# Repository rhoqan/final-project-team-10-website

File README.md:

**<h1 style="text-align:center;"> Improving Pedestrian Safety at Intersections</h1>**
    
<h3 style="text-align:center;"> Shlok Damani, Ryan Ho, Aarav Masrani, Dibyesh Sahoo</h3>

<h3 style="text-align:center;"> Fall 2024</h3>

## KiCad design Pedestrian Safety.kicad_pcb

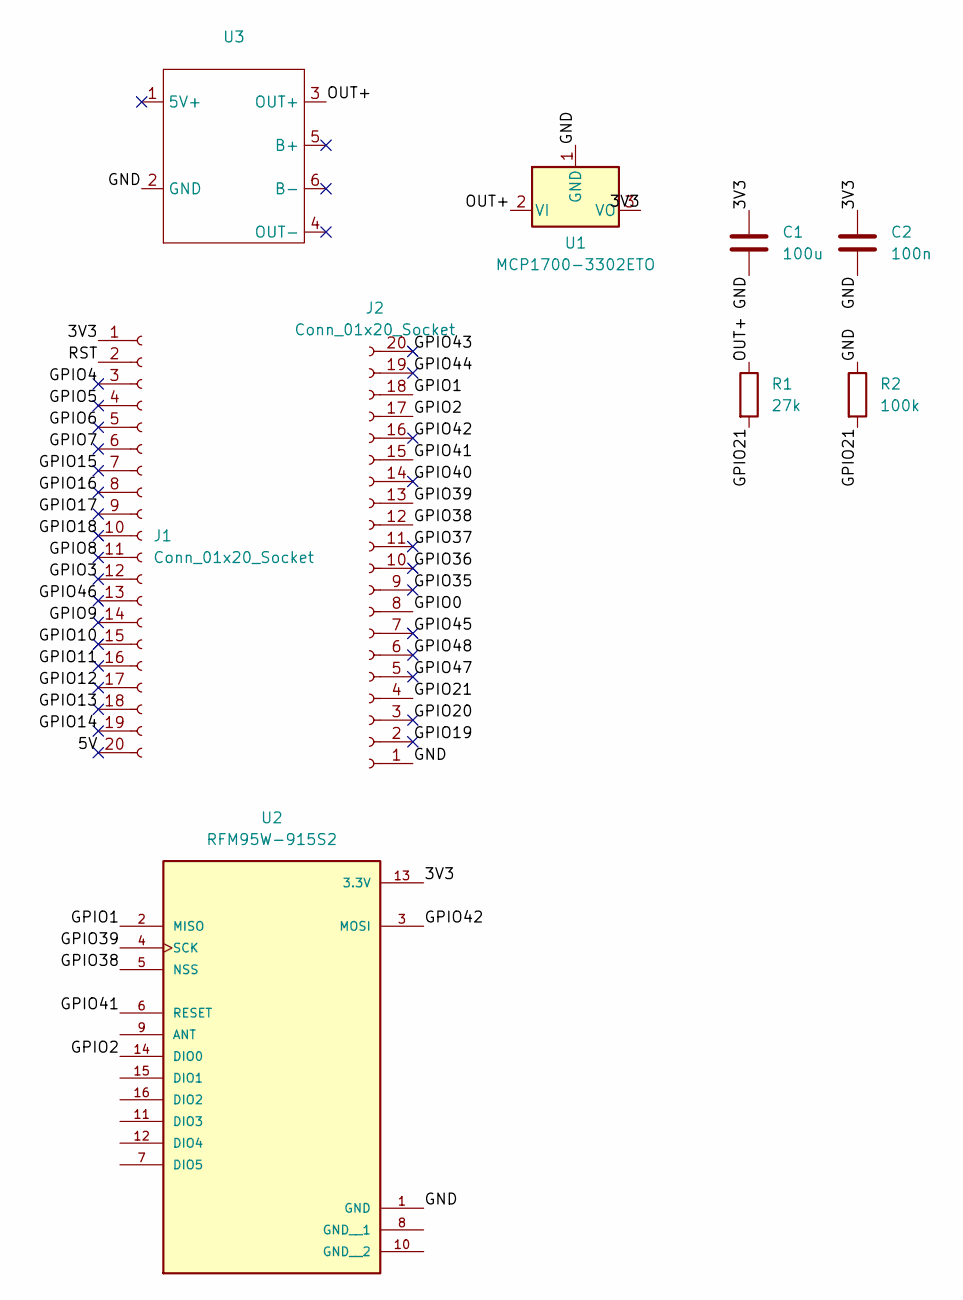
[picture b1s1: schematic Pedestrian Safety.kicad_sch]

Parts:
C1: 100u; CP_Elec_6.3x5.7; Digikey Part Number 732-8419-1-ND
C2: 100n; C_0603_1608Metric; Digikey PN: 1276-1013-1-ND
J1, J2: Conn_01x20_Socket; PinHeader_1x20_P2.54mm_Vertical
R1: 27k; R_0603_1608Metric; Digikey PN: P27.0KHCT-ND
R2: 100k; R_0603_1608Metric; Digikey PN: 311-100KGRCT-ND
U1: MCP1700-3302ETO; TO-92_MC_MCH; Digikey PN: MCP1700-3302E/TO-ND
U2: RFM95W-915S2; XCVR_RFM95W-915S2
U3: TP4056-18650

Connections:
/3V3: C1.1, C2.1, J1.1, U1.3 (VO), U2.13 (3.3V)
/5V: J1.20
/GND: C1.2, C2.2, J2.1, R2.1, U1.1 (GND), U2.1 (GND), U3.2 (GND)
/GPIO0: J2.8
/GPIO1: J2.18, U2.2 (MISO)
/GPIO2: J2.17, U2.14 (DIO0)
/GPIO3: J1.12
/GPIO4: J1.3
/GPIO5: J1.4
/GPIO6: J1.5
/GPIO7: J1.6
/GPIO8: J1.11
/GPIO9: J1.14
/GPIO10: J1.15
/GPIO11: J1.16
/GPIO12: J1.17
/GPIO13: J1.18
/GPIO14: J1.19
/GPIO15: J1.7
/GPIO16: J1.8
/GPIO17: J1.9
/GPIO18: J1.10
/GPIO19: J2.2
/GPIO20: J2.3
/GPIO21: J2.4, R1.2, R2.2
/GPIO35: J2.9
/GPIO36: J2.10
/GPIO37: J2.11
/GPIO38: J2.12, U2.5 (NSS)
/GPIO39: J2.13, U2.4 (SCK)
/GPIO40: J2.14
/GPIO41: J2.15, U2.6 (RESET)
/GPIO42: J2.16, U2.3 (MOSI)
/GPIO43: J2.20
/GPIO44: J2.19
/GPIO45: J2.7
/GPIO46: J1.13
/GPIO47: J2.5
/GPIO48: J2.6
/OUT+: R1.1, U1.2 (VI), U3.3 (OUT+)
/RST: J1.2

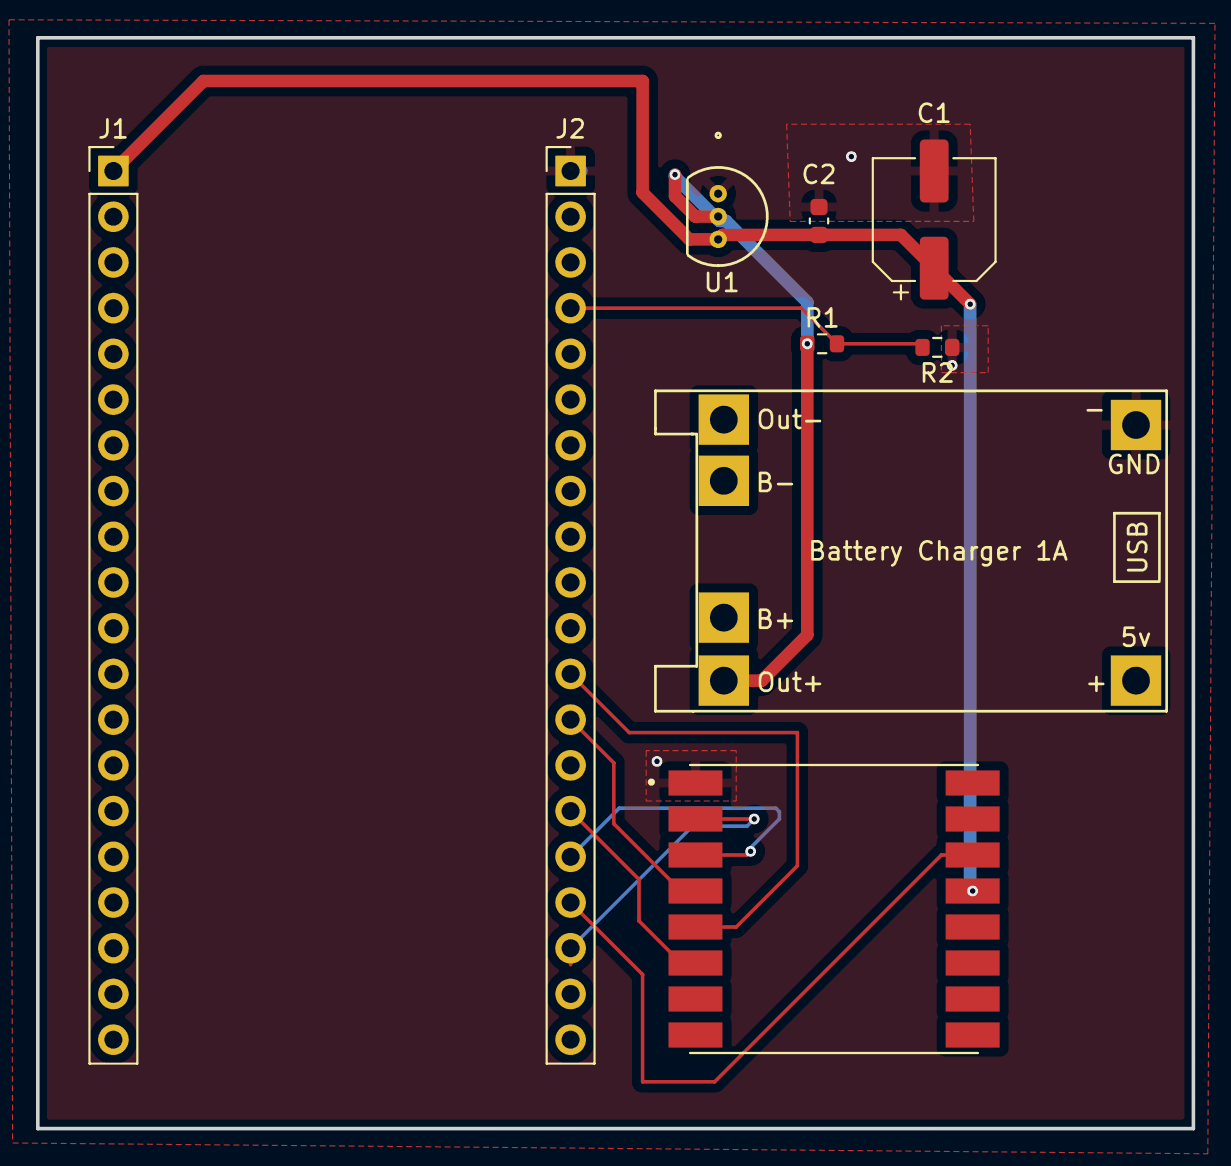
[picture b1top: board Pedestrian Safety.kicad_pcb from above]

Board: 2 copper layers, 64.2 x 60.6 mm, 9 parts (0 on the bottom side), 10 nets.

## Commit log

2024-10-28 PCB Schematic
2024-11-01 Final
2024-11-04 Create test.md
    Test markdown page
2024-11-04 Added folder for website
2024-11-04 Logo
2024-11-05 Removed files unnecessary for website
2024-11-05 Renamed to README
2024-11-05 Update to Match Current Progress
2024-11-05 poster link
2024-11-05 Space for adding stuff
2024-11-05 Fill in information
2024-11-05 Populated Milestones
2024-11-05 Placeholder Headers
2024-11-19 Entries on our team page
2024-11-19 Try to add checkbox
2024-11-19 Content of milestones
2024-11-19 Create Checkboxes
2024-11-20 attempting to resize images
2024-11-20 images uploaded
2024-11-20 diagram
2024-11-23 add plugin
2024-11-23 Beautiful Jekyll
